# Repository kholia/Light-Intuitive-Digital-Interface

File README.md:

#### LiDi

LiDi is Light-Intuitive-Digital-Audio-Interface for µBITX and other radios. It
is meant to be homebrewed on a `Zero PCB` in under 30 minutes.

Design 2:

Design 1:

Note: All the included designs (and some other ones) were simulated in LTspice,
and then tested on air.

Sample testing setup on a breadboard ;)

Sometimes, a quick shorted digital interface is all you need for a US QSO in
"Solar Minimum" conditions ;)

RX performance is lovely with LiDi - US @ -4.

50 QSOs were done with LiDi designs in a single day!

#### BOM Sources

- [Bourns LM-NP-1001-B1L 600:600 audio transformer](https://in.rsdelivers.com/product/bourns/lm-np-1001-b1l/chassis-mount-audio-transformer/1728110)

- [Bourns LM-NP-1001-B1L 600:600 audio transformer (alt source)](https://www.semikart.com/product/bourns-/LM-NP-1001-B1L/58614)

- [Audio & Signal isolation transformer 600:600 (alt source)](https://www.sunrom.com/p/audio-signal-isolation-transformer-600600)

- [GX-16 4-Pin Metal Aviation Plug Female](https://robu.in/product/gx-16-4-pin-metal-aviation-plug-male-and-female-panel-connector/)

- https://projectpoint.in/ (capacitors, pots, connectors)

- https://www.sunrom.com/ (audio connectors, caps, misc)

- https://www.electronicscomp.com/ (connectors, misc)

- https://www.electroncomponents.com/ (connectors, audio cables, misc)

- https://www.diyaudiocart.com/ (nice quality caps)

- [USB Sound Card](https://robu.in/product/5-1-channel-usb-sound-card-for-raspberry-pi-and-computers/)

#### µBITX Aviation Connector Pinout

Clockwise from the notch on the GX-16 connector:

Black + Blue -> Ground

Brown + "Red" -> Speaker

Anti-clockwise from the notch:

Purple -> Mic (TIP)

Orange -> PTT

Brown + "Red" -> Speaker

https://www.hfsignals.com/index.php/ubitx-wire-up/

https://source.android.com/devices/accessories/headset/plug-headset-spec

#### Tips

- Use KD8CEC firmware for µBITX. Use https://github.com/reedbn/ubitxv6 for
  µBITX v6.

- Configure WSJT-X for µBITX using details from the following article.

  http://www.hamskey.com/2018/01/wjst-x-configuration-for-ubitx.html

- For BITX40, use a suitable firmware from https://github.com/amunters.

  I have no experience with BITX40 though.

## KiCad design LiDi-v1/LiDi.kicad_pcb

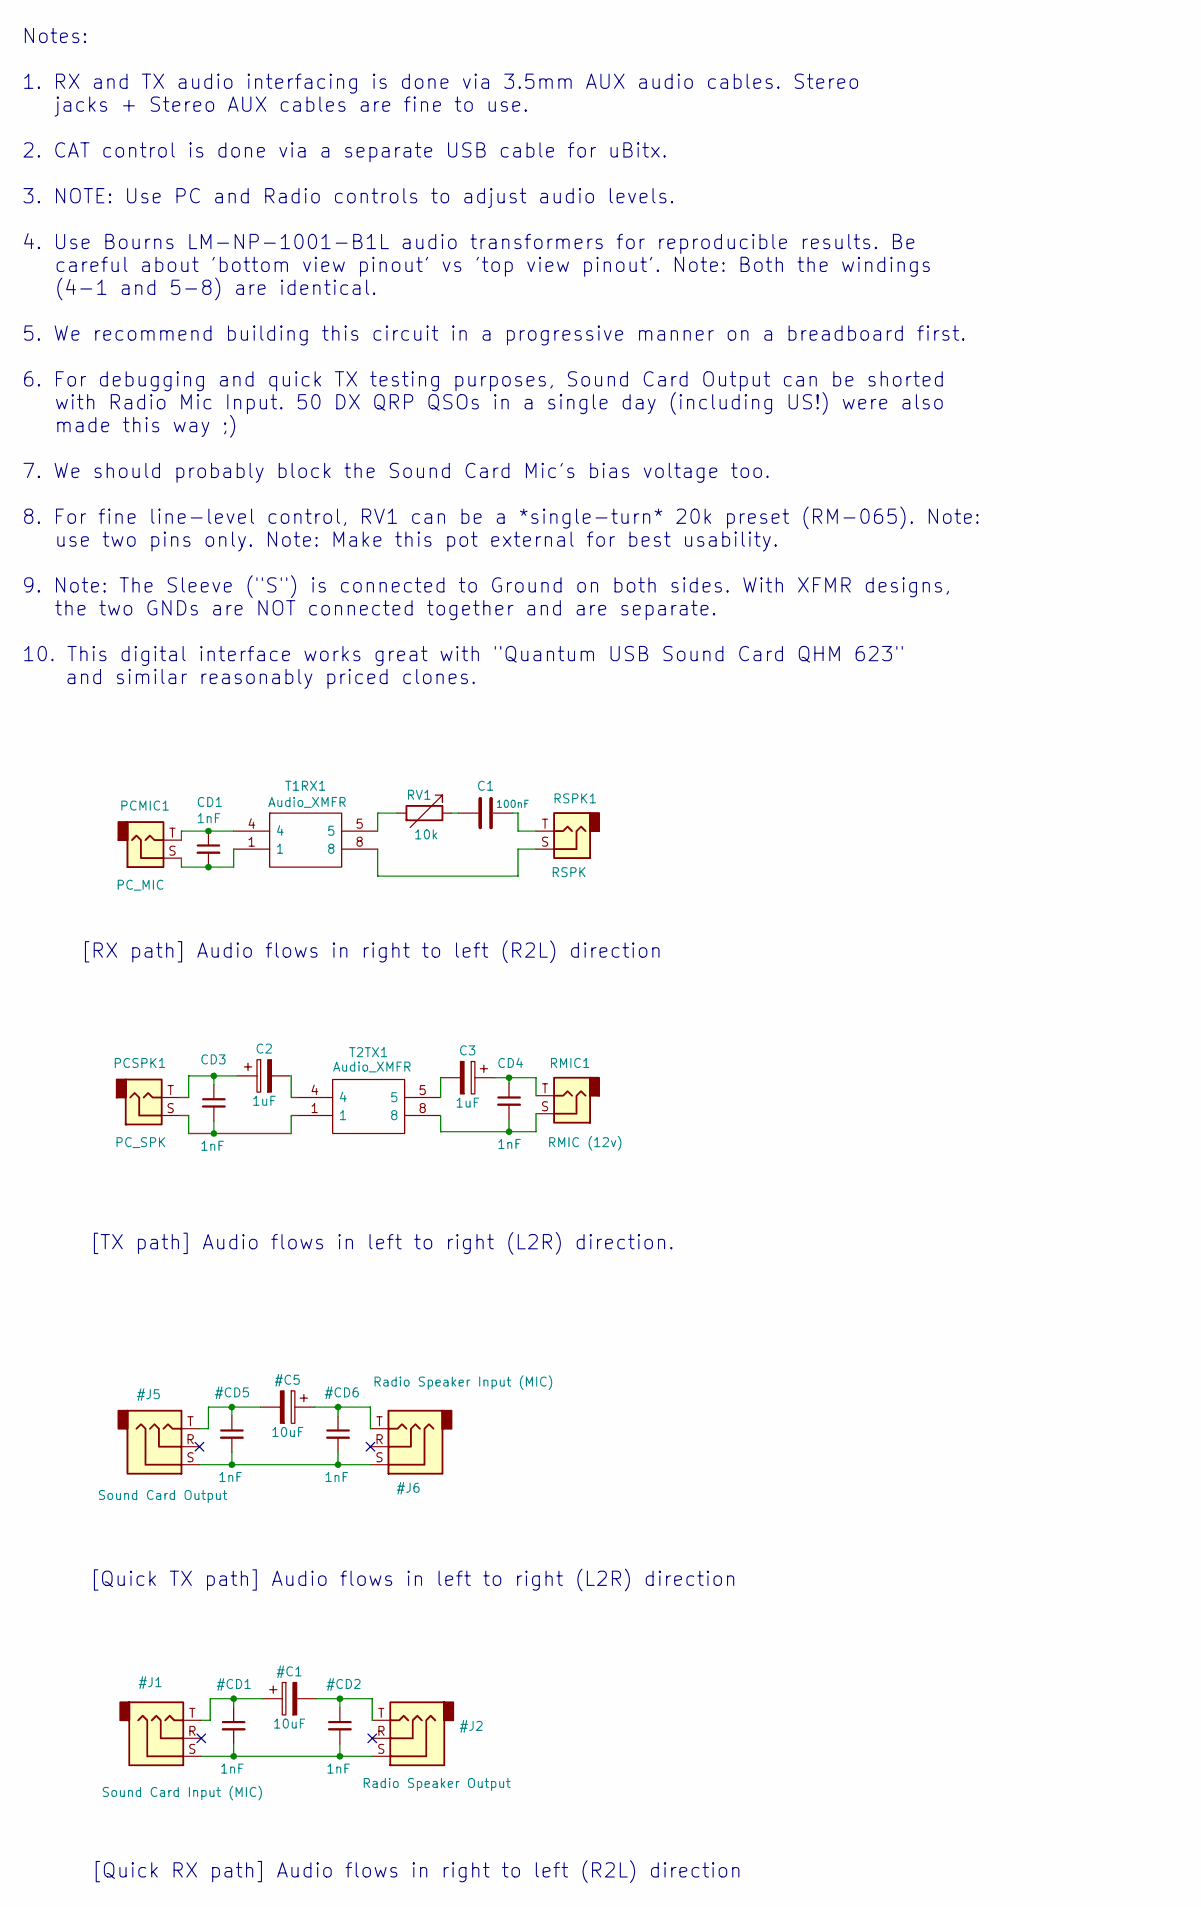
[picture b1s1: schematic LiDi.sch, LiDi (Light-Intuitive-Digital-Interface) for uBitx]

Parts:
C1: 100nF; C_Disc_D3.0mm_W1.6mm_P2.50mm
C2, C3: 1uF; CP_Radial_D6.3mm_P2.50mm
CD1, CD3, CD4: 1nF; C_Disc_D3.0mm_W1.6mm_P2.50mm
PCMIC1: PC_MIC; Custom_PinHeader_1x02_P2.54mm_Vertical
PCSPK1: PC_SPK; Custom_PinHeader_1x02_P2.54mm_Vertical
RMIC1: RMIC (12v); Custom_PinHeader_1x02_P2.54mm_Vertical
RSPK1: RSPK; Custom_PinHeader_1x02_P2.54mm_Vertical
RV1: 10k; Potentiometer_Runtron_RM-063_Horizontal
T1RX1, T2TX1: Audio_XMFR; LMNP1001B1L; Manufacturer_Part_Number LM-NP-1001-B1L; Mouser Part Number 652-LM-NP-1001-B1L

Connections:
unnamed: C1.1, RSPK1.T
unnamed: C1.2, RV1.1
unnamed: C2.1, CD3.1, PCSPK1.T
unnamed: C2.2, T2TX1.4
unnamed: C3.1, CD4.1, RMIC1.T
unnamed: C3.2, T2TX1.5
unnamed: CD1.1, PCMIC1.T, T1RX1.4
unnamed: CD1.2, PCMIC1.S, T1RX1.1
unnamed: CD3.2, PCSPK1.S, T2TX1.1
unnamed: CD4.2, RMIC1.S, T2TX1.8
unnamed: RSPK1.S, T1RX1.8
unnamed: RV1.2, T1RX1.5

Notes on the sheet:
[RX path] Audio flows in right to left (R2L) direction
[TX path] Audio flows in left to right (L2R) direction.
Notes: 1. RX and TX audio interfacing is done via 3.5mm AUX audio cables. Stereo jacks + Stereo AUX cables are fine to use. 2. CAT control is done via a separate USB cable for uBitx. 3. NOTE: Use PC and Radio controls to adjust audio levels. 4. Use Bourns LM-NP-1001-B1L audio transformers for repro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
[Quick TX path] Audio flows in left to right (L2R) direction
[Quick RX path] Audio flows in right to left (R2L) direction

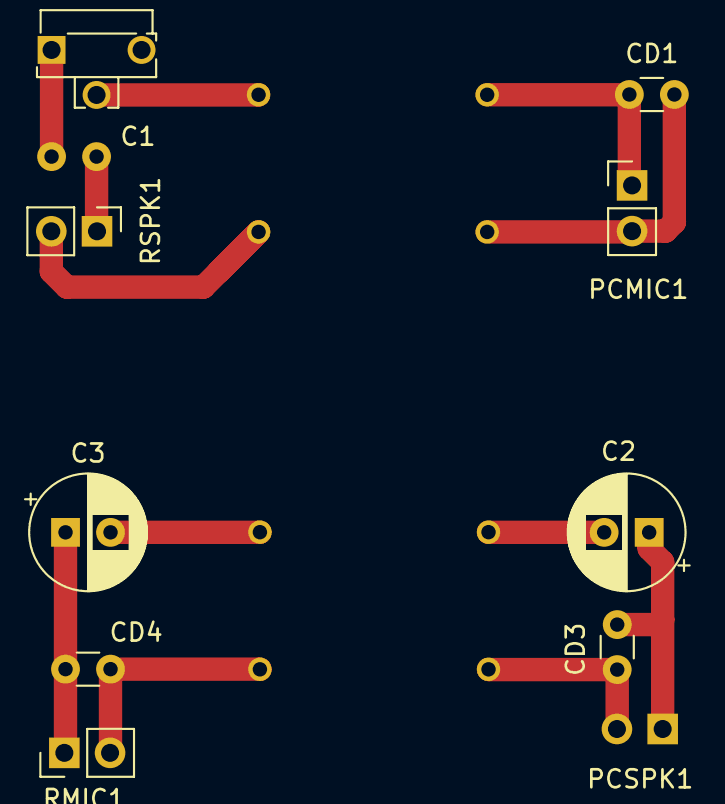
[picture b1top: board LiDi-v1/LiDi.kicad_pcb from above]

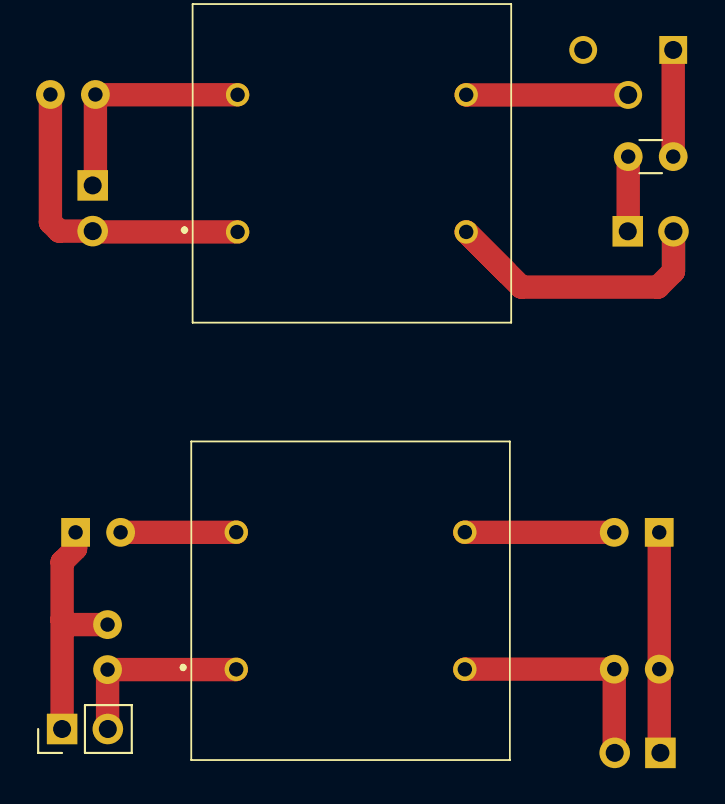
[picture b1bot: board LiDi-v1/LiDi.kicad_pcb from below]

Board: 2 copper layers, 13 parts (4 on the bottom side), 12 nets.

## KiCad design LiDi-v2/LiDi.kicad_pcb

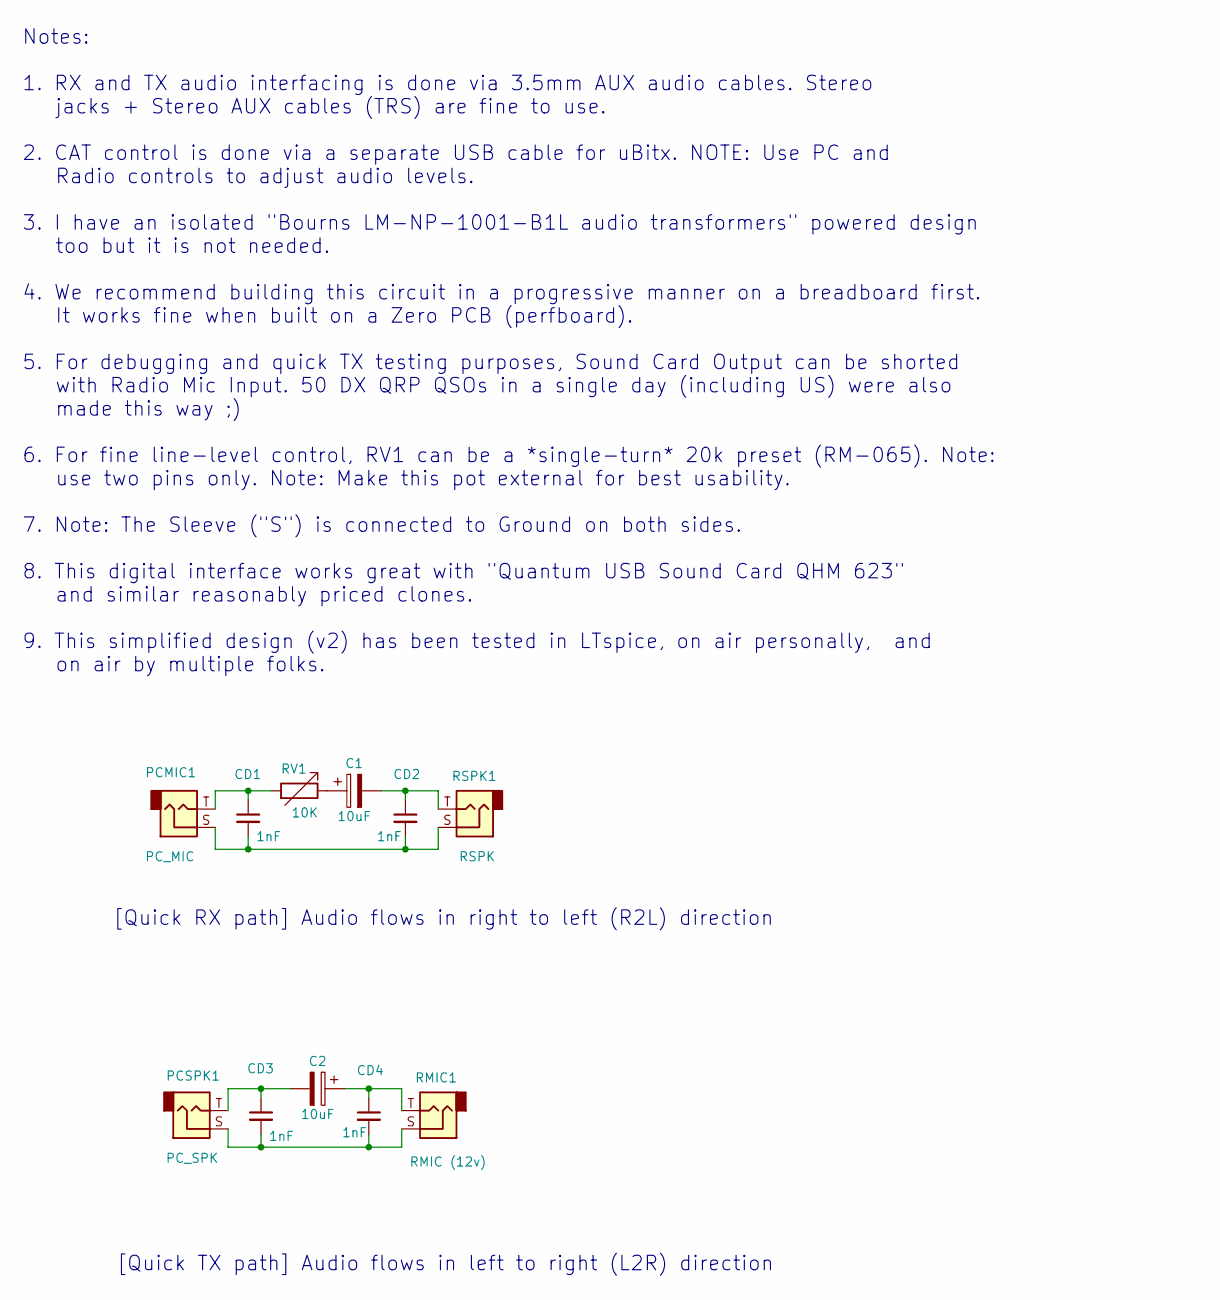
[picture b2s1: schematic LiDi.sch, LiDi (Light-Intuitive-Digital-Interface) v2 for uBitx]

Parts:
C1, C2: 10uF; CP_Radial_D5.0mm_P2.50mm
CD1, CD2, CD3, CD4: 1nF; C_Disc_D3.0mm_W1.6mm_P2.50mm
PCMIC1: PC_MIC; C_Disc_D5.1mm_W3.2mm_P5.00mm
PCSPK1: PC_SPK; C_Disc_D5.1mm_W3.2mm_P5.00mm
RMIC1: RMIC (12v); C_Disc_D5.1mm_W3.2mm_P5.00mm
RSPK1: RSPK; C_Disc_D5.1mm_W3.2mm_P5.00mm
RV1: 10K; 12_C_Disc_D5.1mm_W3.2mm_P5.00mm

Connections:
unnamed: C1.1, RV1.1
unnamed: C1.2, CD2.1, RSPK1.T
unnamed: C2.1, CD4.1, RMIC1.T
unnamed: C2.2, CD3.1, PCSPK1.T
unnamed: CD1.1, PCMIC1.T, RV1.2
unnamed: CD1.2, CD2.2, PCMIC1.S, RSPK1.S
unnamed: CD3.2, CD4.2, PCSPK1.S, RMIC1.S

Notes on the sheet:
[Quick TX path] Audio flows in left to right (L2R) direction
[Quick RX path] Audio flows in right to left (R2L) direction
Notes: 1. RX and TX audio interfacing is done via 3.5mm AUX audio cables. Stereo jacks + Stereo AUX cables (TRS) are fine to use. 2. CAT control is done via a separate USB cable for uBitx. NOTE: Use PC and Radio controls to adjust audio levels. 3. I have an isolated "Bourns LM-NP-1001-B1L audio tra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

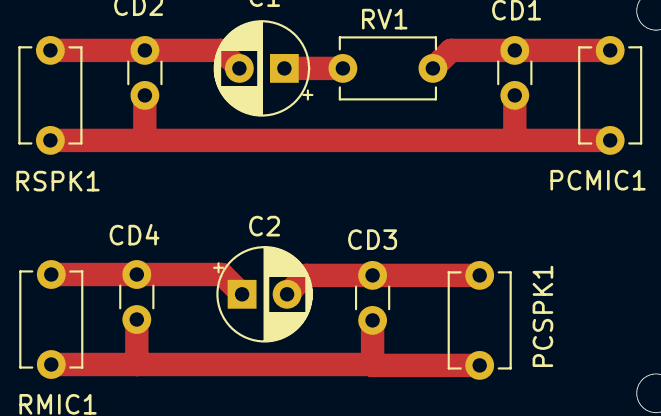
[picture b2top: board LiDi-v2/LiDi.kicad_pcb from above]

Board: 2 copper layers, 11 parts (0 on the bottom side), 7 nets.
